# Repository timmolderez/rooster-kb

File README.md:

# rooster-kb
PCB design + QMK configuration for Rooster, a simple 47-key low-profile ortholinear keyboard

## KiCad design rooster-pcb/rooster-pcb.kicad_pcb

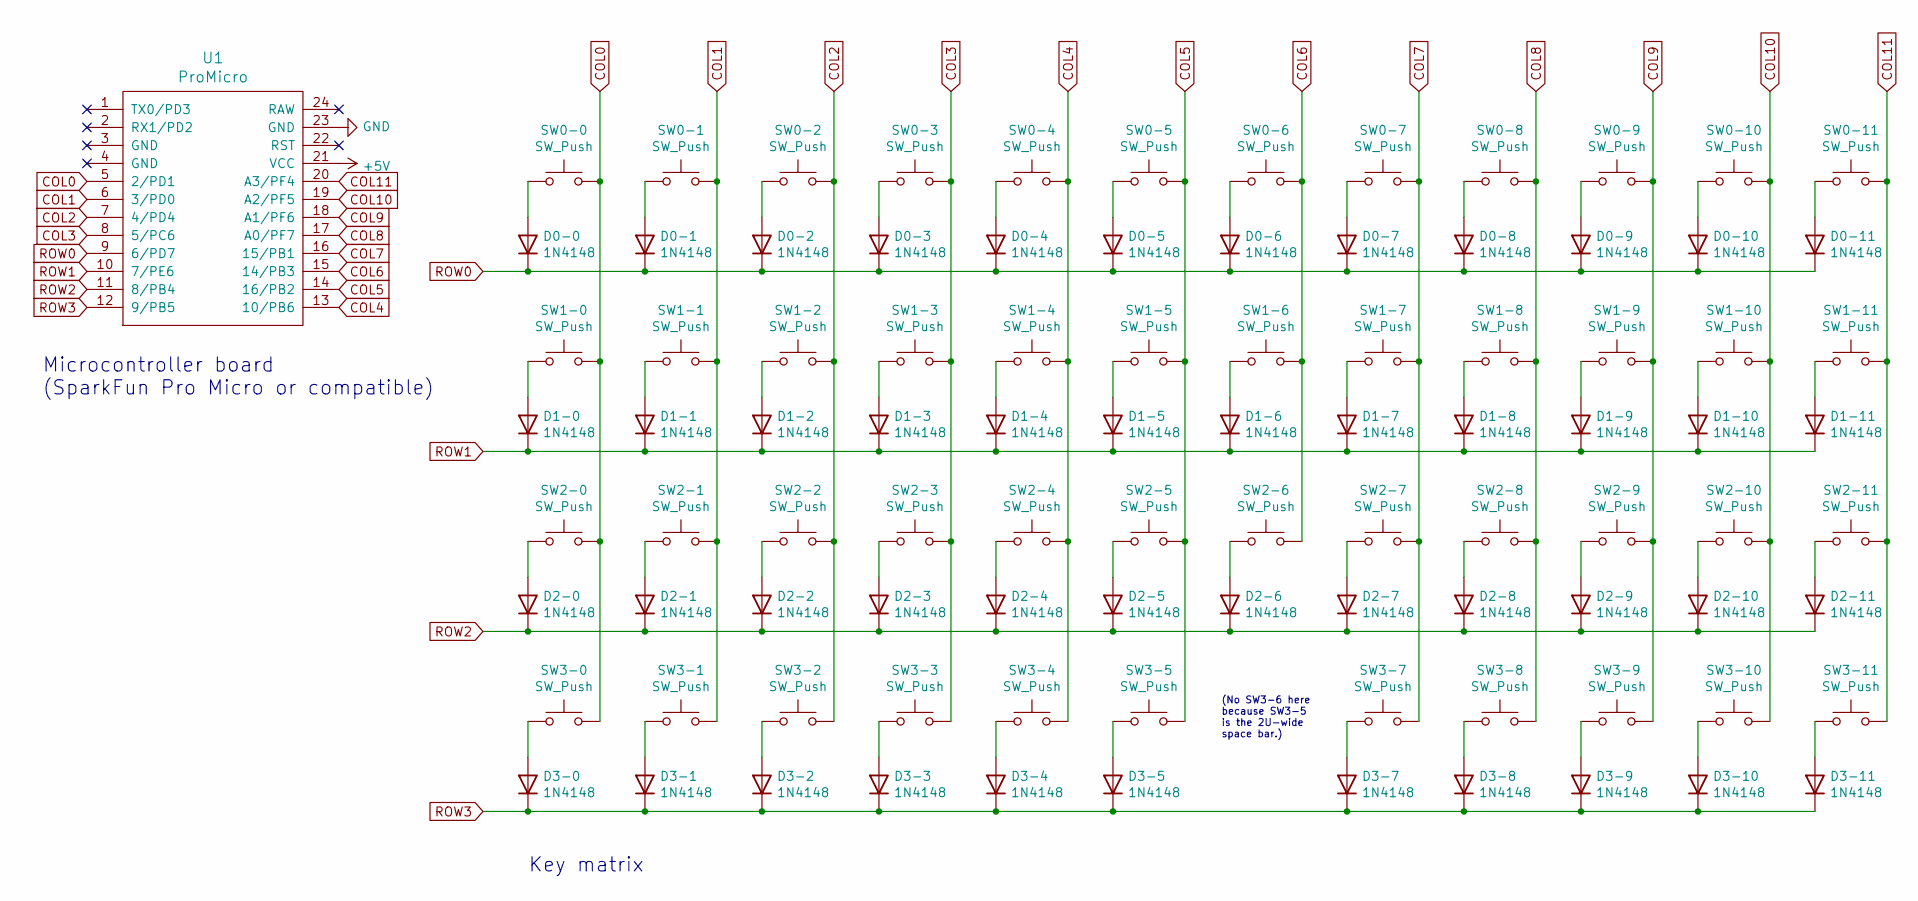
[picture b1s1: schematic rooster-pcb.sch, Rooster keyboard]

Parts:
D0-0, D0-1, D0-2, D0-3, D0-4, D0-5, D0-6, D0-7, D0-8, D0-9, D0-10, D0-11, D1-0, D1-1, D1-2, D1-3, D1-4, D1-5, D1-6, D1-7, D1-8, D1-9, D1-10, D1-11, D2-0, D2-1, D2-2, D2-3, D2-4, D2-5, D2-6, D2-7, D2-8, D2-9, D2-10, D2-11, D3-0, D3-1, D3-2, D3-3, D3-4, D3-5, D3-7, D3-8, D3-9, D3-10, D3-11: 1N4148; D_SOD-123
SW0-0, SW0-1, SW0-2, SW0-3, SW0-4, SW0-5, SW0-6, SW0-7, SW0-8, SW0-9, SW0-10, SW0-11, SW1-0, SW1-1, SW1-2, SW1-3, SW1-4, SW1-5, SW1-6, SW1-7, SW1-8, SW1-9, SW1-10, SW1-11, SW2-0, SW2-1, SW2-2, SW2-3, SW2-4, SW2-5, SW2-6, SW2-7, SW2-8, SW2-9, SW2-10, SW2-11, SW3-0, SW3-1, SW3-2, SW3-3, SW3-4, SW3-5, SW3-7, SW3-8, SW3-9, SW3-10, SW3-11: SW_Push; SW_PG1350
U1: ProMicro; ArduinoProMicro

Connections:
+5V: U1.21 (VCC)
COL0: SW0-0.2, SW1-0.2, SW2-0.2, SW3-0.2, U1.5 (2/PD1)
COL1: SW0-1.2, SW1-1.2, SW2-1.2, SW3-1.2, U1.6 (3/PD0)
COL2: SW0-2.2, SW1-2.2, SW2-2.2, SW3-2.2, U1.7 (4/PD4)
COL3: SW0-3.2, SW1-3.2, SW2-3.2, SW3-3.2, U1.8 (5/PC6)
COL4: SW0-4.2, SW1-4.2, SW2-4.2, SW3-4.2, U1.13 (10/PB6)
COL5: SW0-5.2, SW1-5.2, SW2-5.2, SW3-5.2, U1.14 (16/PB2)
COL6: SW0-6.2, SW1-6.2, SW2-6.2, U1.15 (14/PB3)
COL7: SW0-7.2, SW1-7.2, SW2-7.2, SW3-7.2, U1.16 (15/PB1)
COL8: SW0-8.2, SW1-8.2, SW2-8.2, SW3-8.2, U1.17 (A0/PF7)
COL9: SW0-9.2, SW1-9.2, SW2-9.2, SW3-9.2, U1.18 (A1/PF6)
COL10: SW0-10.2, SW1-10.2, SW2-10.2, SW3-10.2, U1.19 (A2/PF5)
COL11: SW0-11.2, SW1-11.2, SW2-11.2, SW3-11.2, U1.20 (A3/PF4)
GND: U1.23 (GND)
unnamed: D0-0.2 (A), SW0-0.1
unnamed: D0-1.2 (A), SW0-1.1
unnamed: D0-2.2 (A), SW0-2.1
unnamed: D0-3.2 (A), SW0-3.1
unnamed: D0-4.2 (A), SW0-4.1
unnamed: D0-5.2 (A), SW0-5.1
unnamed: D0-6.2 (A), SW0-6.1
unnamed: D0-7.2 (A), SW0-7.1
unnamed: D0-8.2 (A), SW0-8.1
unnamed: D0-9.2 (A), SW0-9.1
unnamed: D0-10.2 (A), SW0-10.1
unnamed: D0-11.2 (A), SW0-11.1
unnamed: D1-0.2 (A), SW1-0.1
unnamed: D1-1.2 (A), SW1-1.1
unnamed: D1-2.2 (A), SW1-2.1
unnamed: D1-3.2 (A), SW1-3.1
unnamed: D1-4.2 (A), SW1-4.1
unnamed: D1-5.2 (A), SW1-5.1
unnamed: D1-6.2 (A), SW1-6.1
unnamed: D1-7.2 (A), SW1-7.1
unnamed: D1-8.2 (A), SW1-8.1
unnamed: D1-9.2 (A), SW1-9.1
unnamed: D1-10.2 (A), SW1-10.1
unnamed: D1-11.2 (A), SW1-11.1
unnamed: D2-0.2 (A), SW2-0.1
unnamed: D2-1.2 (A), SW2-1.1
unnamed: D2-2.2 (A), SW2-2.1
unnamed: D2-3.2 (A), SW2-3.1
unnamed: D2-4.2 (A), SW2-4.1
unnamed: D2-5.2 (A), SW2-5.1
unnamed: D2-6.2 (A), SW2-6.1
unnamed: D2-7.2 (A), SW2-7.1
unnamed: D2-8.2 (A), SW2-8.1
unnamed: D2-9.2 (A), SW2-9.1
unnamed: D2-10.2 (A), SW2-10.1
unnamed: D2-11.2 (A), SW2-11.1
unnamed: D3-0.2 (A), SW3-0.1
unnamed: D3-1.2 (A), SW3-1.1
unnamed: D3-2.2 (A), SW3-2.1
unnamed: D3-3.2 (A), SW3-3.1
unnamed: D3-4.2 (A), SW3-4.1
unnamed: D3-5.2 (A), SW3-5.1
unnamed: D3-7.2 (A), SW3-7.1
unnamed: D3-8.2 (A), SW3-8.1
unnamed: D3-9.2 (A), SW3-9.1
unnamed: D3-10.2 (A), SW3-10.1
unnamed: D3-11.2 (A), SW3-11.1
ROW0: D0-0.1 (K), D0-1.1 (K), D0-2.1 (K), D0-3.1 (K), D0-4.1 (K), D0-5.1 (K), D0-6.1 (K), D0-7.1 (K), D0-8.1 (K), D0-9.1 (K), D0-10.1 (K), D0-11.1 (K), U1.9 (6/PD7)
ROW1: D1-0.1 (K), D1-1.1 (K), D1-2.1 (K), D1-3.1 (K), D1-4.1 (K), D1-5.1 (K), D1-6.1 (K), D1-7.1 (K), D1-8.1 (K), D1-9.1 (K), D1-10.1 (K), D1-11.1 (K), U1.10 (7/PE6)
ROW2: D2-0.1 (K), D2-1.1 (K), D2-2.1 (K), D2-3.1 (K), D2-4.1 (K), D2-5.1 (K), D2-6.1 (K), D2-7.1 (K), D2-8.1 (K), D2-9.1 (K), D2-10.1 (K), D2-11.1 (K), U1.11 (8/PB4)
ROW3: D3-0.1 (K), D3-1.1 (K), D3-2.1 (K), D3-3.1 (K), D3-4.1 (K), D3-5.1 (K), D3-7.1 (K), D3-8.1 (K), D3-9.1 (K), D3-10.1 (K), D3-11.1 (K), U1.12 (9/PB5)

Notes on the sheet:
(No SW3-6 here because SW3-5 is the 2U-wide space bar.)
Microcontroller board (SparkFun Pro Micro or compatible)
Key matrix

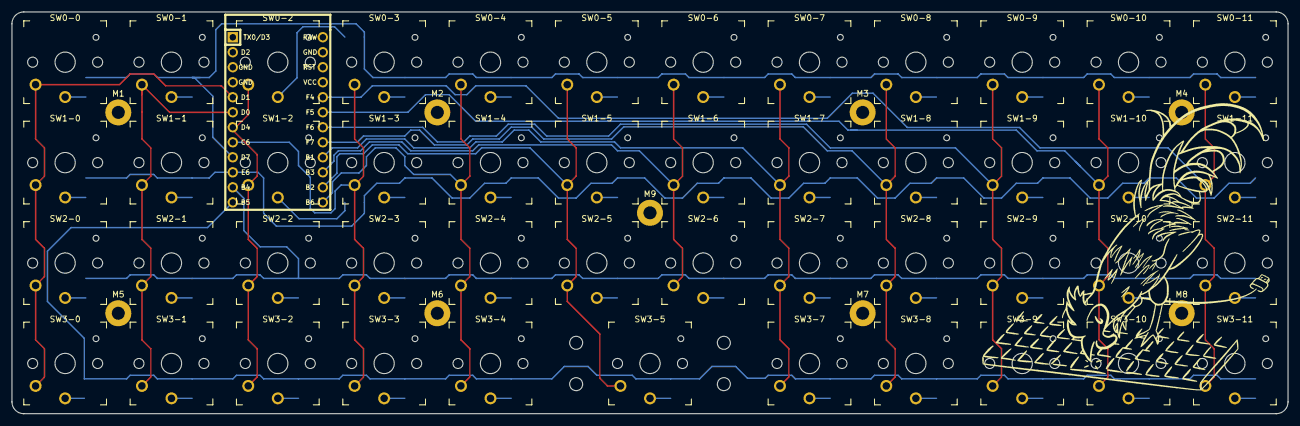
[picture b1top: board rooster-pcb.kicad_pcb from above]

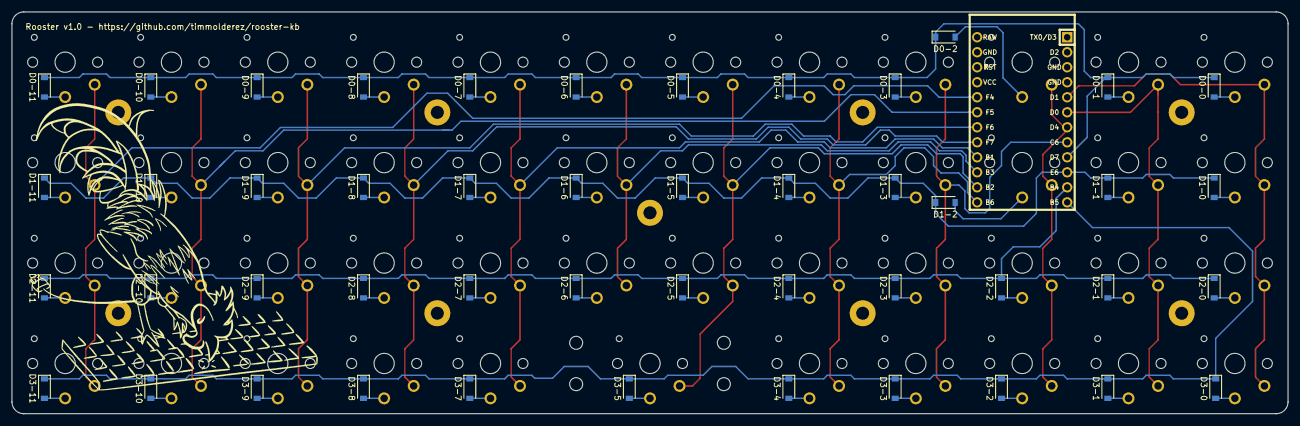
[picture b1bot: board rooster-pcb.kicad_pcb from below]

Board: 2 copper layers, 216.0 x 68.0 mm, 108 parts (47 on the bottom side), 63 nets.

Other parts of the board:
M1, M2, M3, M4, M5, M6, M7, M8, M9: MountingHole_2.2mm_M2_Pad
N1, N2, N3, N4: MountingHole_2.2mm_M2

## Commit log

2021-01-31 Added KiCad libraries
2021-01-31 Added .gitignore
2021-01-31 Added current PCB version
2021-02-03 Replaced ProMicro symbol & footprint; adding mounting holes
2021-02-03 Remove unused Kicad library
2021-02-03 Positioned diodes
2021-02-04 Flipped diodes to back side; started tracing columns
2021-02-04 Adding horizontal traces
2021-02-05 Finished routing; design rules passed
2021-02-06 Remade PCB for 0.5mm spacing between keycaps + surface-mounted diodes
2021-08-01 Added Rooster graphics
2021-08-02 Added Gerber files
2021-08-05 Rooster v1.0 gerbers ready for manufacturing!
2021-08-26 Added QMK config files; it works!
